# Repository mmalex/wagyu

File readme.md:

# 'wagyu' simple 5hp eurorack module to demonstrate STM32F405 based module design. 
## what is it?

WATCH THIS -  https://www.youtube.com/watch?v=Wm21Wc7AefM

a small eurorack module with 3 knobs, 4 DC coupled CV inputs (+-5v), an encoder, an 8x8 LED matrix display, stereo AC coupled outputs (+-8v), and stereo AC coupled audio rate inputs. the audio inputs are 'aliased' with two of the CV inputs, so that you can use one or both of them as either CV or audio inputs. for example, the 3 leftmost jacks can be used as CV inputs, then the 3 rightmost jacks are the 'audio' side, with mono in at the top and stereo out at the bottom. alternatively, the top two jacks can be used as stereo inputs.

it has an STM32F405 processor at 168Mhz, which is fast enough to do fun reverby, synthy things. it's also cheap and in-stock at JLC :)

## but what does it DO? 

it teaches me module design, and latterly, you - thru a series of (so far 2) youtube streams.

this repo is a dump of the state of the hardware design files and software as written on-stream.
the first stream was more hardware centric, but not about this specific design - https://www.youtube.com/watch?v=Xf4CxC8exFM
the second stream covered bringing up the entire sw/ folder from scratch for this design - https://www.youtube.com/watch?v=Wm21Wc7AefM

## Hardware
the files are presented in the exact state I showed on stream and submitted to JLCPCB for PCB manufacture and assembly. at the time, all SMT parts were in-stock and from their standard library. the front panel is presented as two designs that can be broken apart. I wasnt sure if 'holes' or 'no-solder-mask-circuitboard' would be better; in the end, only holes worked - so if you are submitting this, you can save yourself some money by removing the 'no-holes' half of the front panel design, by editing the kicad files and regenerating the gerbers.

the main board is a 4 layer design, mostly auto routed (sorry not sorry). It has 3 mistakes, none fatal: the euro power jack isnt perfectly centered, which causes the plastic plug to overhang by a mm or so. annoying, and could be fixed by shuffling it over a bit. it's fine if your case or the adjacent module has a bit of space there :). the I2C bus doesn't have pullups, oops; you need two 2.2k resistors pulling up to 3v3 adding. I work around this in software so it works fine without (I bit bang the I2C and go slow, using the STM's on-chip pullups). lastly, the footprint of the 8x8 LED matrix I mistakenly assumed the pins were in a square; they are not. see second video for more info, but you can just bend them and it fits. Just.

## BOM
all the SMT positioning (csv) that you can upload to JLC's assembly service is in the assembly/ subfolder; likewise, the SMT BOM with part numbers for the lcsc.com site - all chosen to be available for JLC assembly.
Once you receive the board, you need to source and add your own 'hardware':
- 3 linear taper pots, 50k -100k maybe? I got mine from thonk.co.uk, Vertical T-18 https://www.thonk.co.uk/shop/alpha-9mm-pots-vertical-t18/
- 6 thonkiconn jacks, also from thonk.co.uk
- an encoder with clicky button. eg https://www.digikey.co.uk/product-detail/en/bourns-inc/PEC11R-4215F-S0024/PEC11R-4215F-S0024-ND/4499665
- some knobs! from thonk.co.uk again.
- a 0.8" LED 8x8 matrix (single color). I got mine from adafruit, it says 'luckylight' on the side. mine was white, here's a red one: https://www.adafruit.com/product/454. in the UK, pimeroni is a great stockist of adafruit stuff.
- a eurorack 8x2 0.1" spacing male pin header for power. I stupidly soldered a right angled one onto mine- it does fit! but simpler would have just been to use bog standard 0.1" header pins, in 2 rows, and make sure to plug them into a plug before soldering to keep them at the right angle. I object to regulating 12v straight down to 3v3 and boiling the oceans - so its a 16 pin plug (for 5v). tough!
- a programming header - I use the 'STDC14 pinout' (google it), which puts a Uart along with classic SWD pins. The PCB expects a surface mount 7x2 0.05" spacing pin header. for example https://www.digikey.co.uk/product-detail/en/amphenol-icc-fci/20021121-00014T4LF/609-3730-ND/2209080. or you can just solder 4 bodge wires on over to your SWD programmer.

## SW
the software is as I left it at the end of the second stream. We've brought up all the hardware except audio input; the only files that differ from the autogenerated project are main.c and codec.h; everything else is ignorable boilerplate.
it doesn't do anything musical at this stage, but it should make a good starting point.

## stuff you might need
you need STMCube32IDE for free from ST.com to do the software side; runs on mac, windows and linux.
I used a Digilent Analog Discovery 2 as a scope & signal generator, but you don't strictly need it.
you will need some way to flash your board - an ST Link programmer for example; the new ST Link 3 Mini has exactly the right programming header, but I can't seem to find one to buy! instead, I use Nucleo boards (look on amazon for 'nucleo STM32') - they are typically under £20, give you a great prototyping platform AND a built in ST Link programmer you can use on your own standalone boards.

have fun! let me know on twitter if you get something out of this! twitter.com/mmalex

## License
I'm releasing this all into the public domain. the hardware is heavily inspired by the eurorack open source modules, and the codec & cpu parts are pretty generic.  I would appreciate if you let me know if you get any value out of this! let me know on twitter @mmalex.

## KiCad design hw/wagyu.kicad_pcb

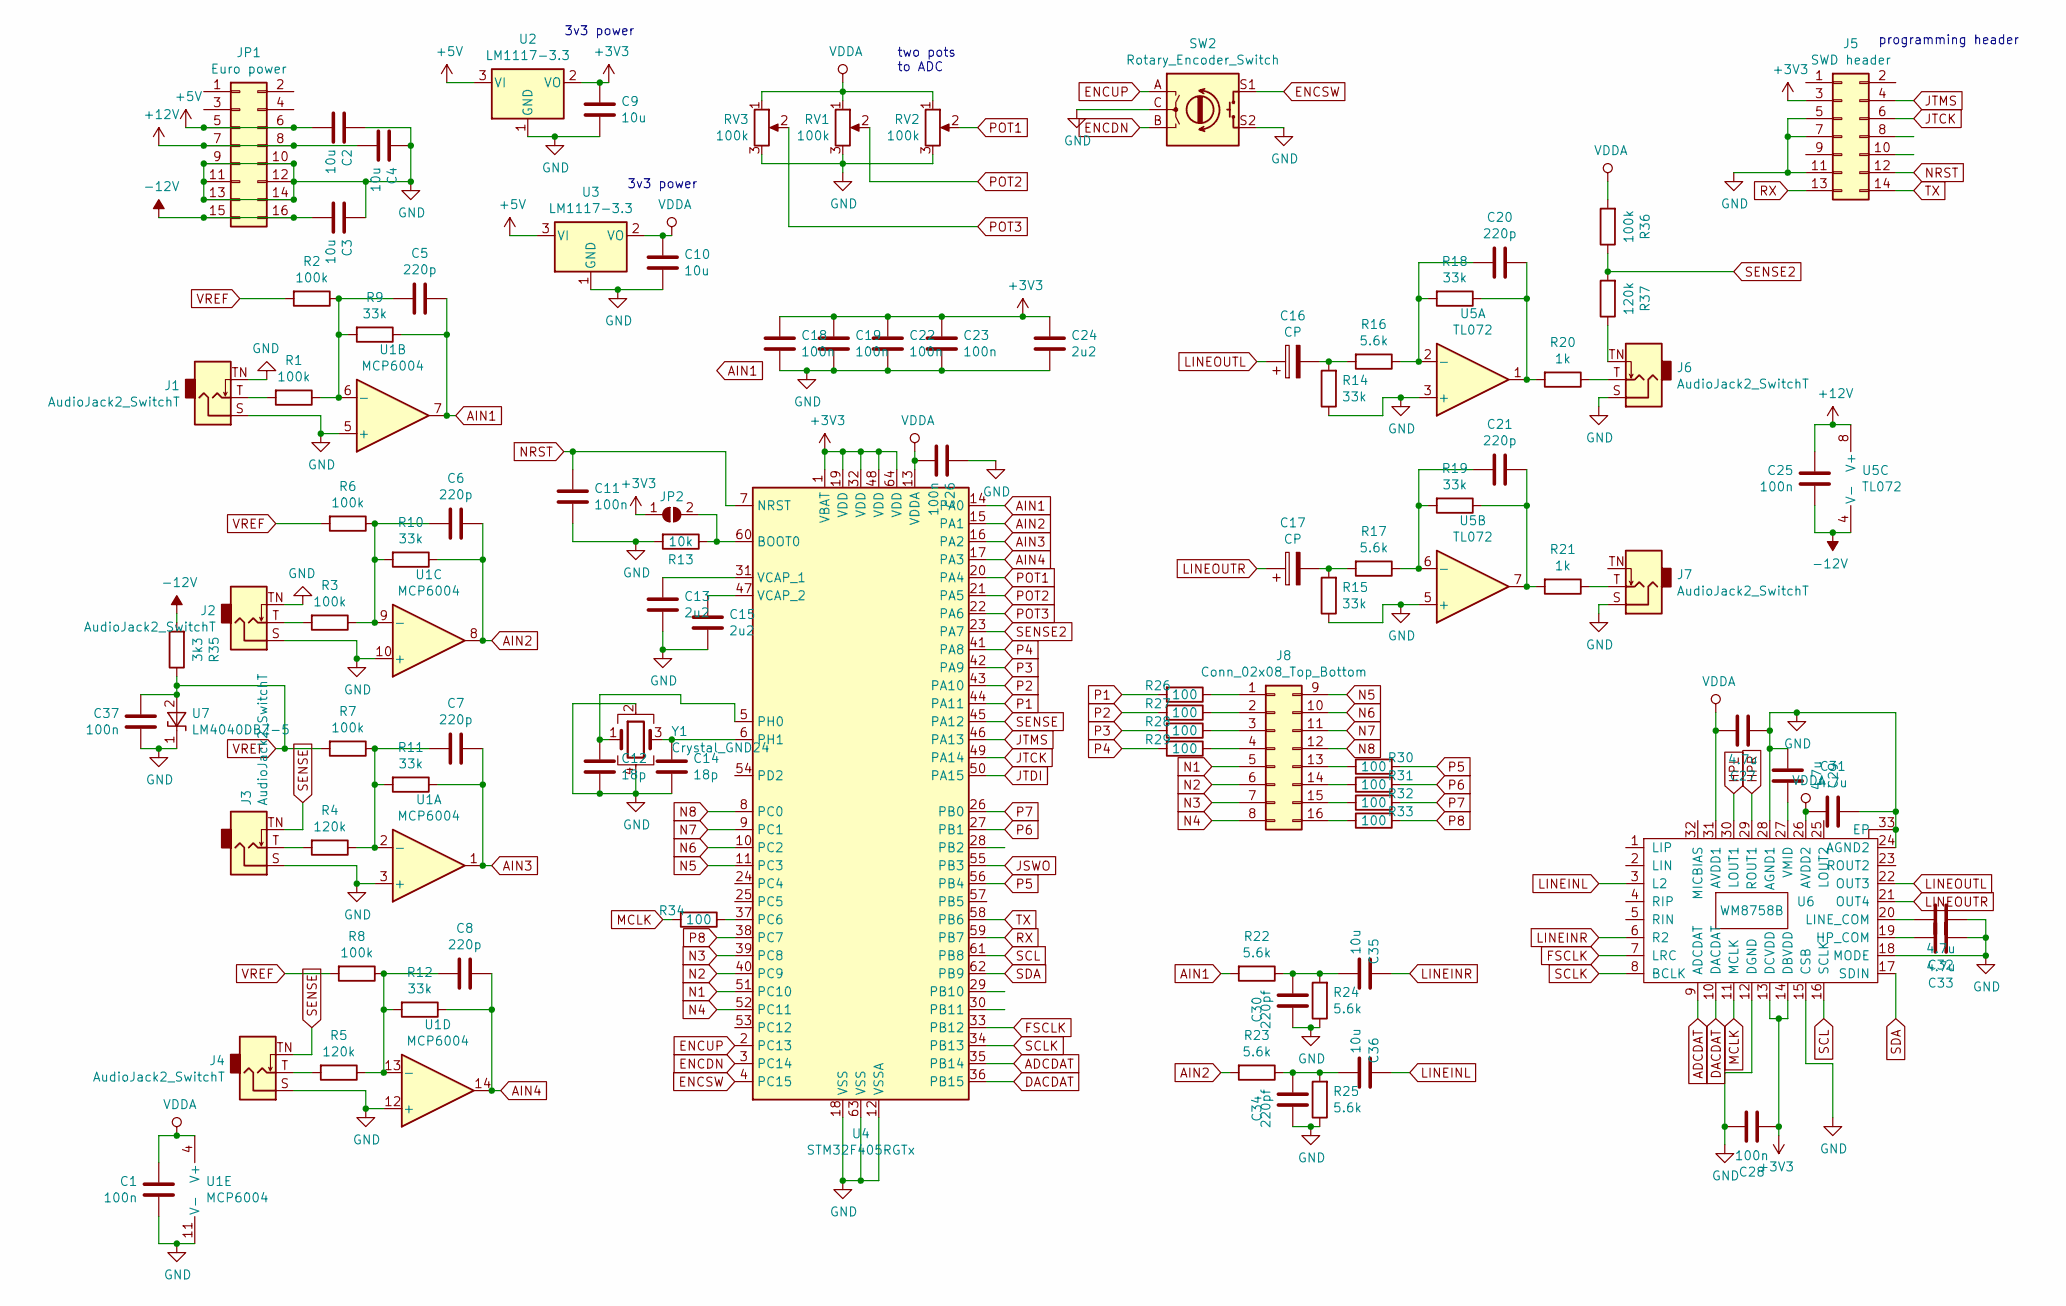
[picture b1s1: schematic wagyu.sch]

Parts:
C1, C11, C18, C19, C22, C23, C25, C26, C37: 100n; C_0603_1608Metric
C2, C3, C4, C9, C10, C35, C36: 10u; C_0805_2012Metric
C5, C6, C7, C8, C20, C21: 220p; C_0603_1608Metric
C12, C14: 18p; C_0603_1608Metric
C13, C15, C24: 2u2; C_0603_1608Metric
C16, C17: CP; CP_Elec_5x4.5
C27, C29, C31, C32, C33: 4.7u; C_0603_1608Metric
C28: 100n; C_0603_1608Metric; LCSC C19666
C30, C34: 220pf; C_0603_1608Metric
J1, J2, J3, J4, J6, J7: AudioJack2_SwitchT; Jack_3.5mm_QingPu_WQP-PJ398SM_Vertical_CircularHoles
J5: SWD header; PinHeader_2x07_P1.27mm_Vertical_SMD
J8: Conn_02x08_Top_Bottom; led8x8
JP1: Euro power; PinHeader_2x08_P2.54mm_Vertical
JP2: SolderJumper_2_Open; SolderJumper-2_P1.3mm_Open_Pad1.0x1.5mm
R1, R2, R3, R6, R7, R8, R36: 100k; R_0603_1608Metric
R4, R5, R37: 120k; R_0603_1608Metric
R9, R10, R11, R12, R14, R15, R18, R19: 33k; R_0603_1608Metric
R13: 10k; R_0603_1608Metric
R16, R17, R22, R23, R24, R25: 5.6k; R_0603_1608Metric
R20, R21: 1k; R_0603_1608Metric
R26, R27, R28, R29, R30, R31, R32, R33, R34: 100; R_0603_1608Metric
R35: 3k3; R_0603_1608Metric
RV1, RV2, RV3: 100k; Potentiometer_Alpha_RD901F-40-00D_Single_Vertical
SW2: Rotary_Encoder_Switch; RotaryEncoder_Alps_EC11E-Switch_Vertical_H20mm
U1: MCP6004; TSSOP-14_4.4x5mm_P0.65mm
U2, U3: LM1117-3.3; SOT-223-3_TabPin2
U4: STM32F405RGTx; LQFP-64_10x10mm_P0.5mm
U5: TL072; SOIC-8_3.9x4.9mm_P1.27mm
U6: WM8758B; QFN-32-1EP_5x5mm_P0.5mm_EP3.45x3.45mm; LCSC C323840
U7: LM4040DBZ-5; SOT-23
Y1: Crystal_GND24; Crystal_SMD_Abracon_ABM8G-4Pin_3.2x2.5mm

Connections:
+3V3: C9.1, C18.1, C19.1, C22.1, C23.1, C24.1, C28.2, J5.3, JP2.1 (A), U2.2 (VO), U4.1 (VBAT), U4.19 (VDD), U4.32 (VDD), U4.48 (VDD), U4.64 (VDD), U6.13 (DCVDD), U6.14 (DBVDD)
+5V: C2.2, JP1.5, JP1.6, U2.3 (VI), U3.3 (VI)
+12V: C4.2, C25.2, JP1.7, JP1.8, U5.8 (V+)
-12V: C3.2, C25.1, JP1.15, JP1.16, R35.2, U5.4 (V-)
ADCDAT: U4.35 (PB14), U6.9 (ADCDAT)
AIN1: C5.1, R9.1, R22.2, U1.7, U4.14 (PA0)
AIN2: C6.1, R10.1, R23.2, U1.8, U4.15 (PA1)
AIN3: C7.1, R11.1, U1.1, U4.16 (PA2)
AIN4: C8.1, R12.1, U1.14, U4.17 (PA3)
DACDAT: U4.36 (PB15), U6.10 (DACDAT)
ENCDN: SW2.B, U4.3 (PC14)
ENCSW: SW2.S1, U4.4 (PC15)
ENCUP: SW2.A, U4.2 (PC13)
FSCLK: U4.33 (PB12), U6.7 (LRC)
GND: C1.1, C2.1, C3.1, C4.1, C9.2, C10.2, C11.2, C12.2, C13.2, C14.2, C15.2, C18.2, C19.2, C22.2, C23.2, C24.2, C26.1, C27.2, C28.1, C29.2, C30.1, C31.1, C32.2, C33.2, C34.1, C37.1, J1.S, J1.TN, J2.S, J2.TN, J3.S, J4.S, J5.5, J5.7, J5.11, J6.S, J7.S, JP1.9, JP1.10, JP1.11, JP1.12, JP1.13, JP1.14, R13.2, R14.1, R15.1, R24.1, R25.1, RV1.3, RV2.3, RV3.3, SW2.C, SW2.S2, U1.3 (+), U1.5 (+), U1.10 (+), U1.11 (V-), U1.12 (+), U2.1 (GND), U3.1 (GND), U4.12 (VSSA), U4.18 (VSS), U4.63 (VSS), U5.3 (+), U5.5 (+), U6.12 (DGND), U6.15 (CSB), U6.18 (MODE), U6.24 (AGND2), U6.28 (AGND1), U6.33 (EP), U7.1 (K), Y1.2, Y1.4
HPL: U6.30 (LOUT1)
HPR: U6.29 (ROUT1)
JSWO: U4.55 (PB3)
JTCK: J5.6, U4.49 (PA14)
JTDI: U4.50 (PA15)
JTMS: J5.4, U4.46 (PA13)
LINEINL: C36.1, U6.3 (L2)
LINEINR: C35.1, U6.6 (R2)
LINEOUTL: C16.1, U6.22 (OUT3)
LINEOUTR: C17.1, U6.21 (OUT4)
MCLK: R34.2, U6.11 (MCLK)
N1: J8.5, U4.51 (PC10)
N2: J8.6, U4.40 (PC9)
N3: J8.7, U4.39 (PC8)
N4: J8.8, U4.52 (PC11)
N5: J8.9, U4.11 (PC3)
N6: J8.10, U4.10 (PC2)
N7: J8.11, U4.9 (PC1)
N8: J8.12, U4.8 (PC0)
NRST: C11.1, J5.12, U4.7 (NRST)
unnamed: C5.2, R1.1, R2.1, R9.2, U1.6 (-)
unnamed: C6.2, R3.1, R6.1, R10.2, U1.9 (-)
unnamed: C7.2, R4.1, R7.1, R11.2, U1.2 (-)
unnamed: C8.2, R5.1, R8.1, R12.2, U1.13 (-)
unnamed: C12.1, U4.5 (PH0), Y1.1
unnamed: C13.1, U4.31 (VCAP_1)
unnamed: C14.1, U4.6 (PH1), Y1.3
unnamed: C15.1, U4.47 (VCAP_2)
unnamed: C16.2, R14.2, R16.2
unnamed: C17.2, R15.2, R17.2
unnamed: C20.1, R18.1, R20.2, U5.1
unnamed: C20.2, R16.1, R18.2, U5.2 (-)
unnamed: C21.1, R19.1, R21.2, U5.7
unnamed: C21.2, R17.1, R19.2, U5.6 (-)
unnamed: C29.1, U6.27 (VMID)
unnamed: C30.2, C35.2, R22.1, R24.2
unnamed: C32.1, U6.20 (LINE_COM)
unnamed: C33.1, U6.19 (HP_COM)
unnamed: C34.2, C36.2, R23.1, R25.2
unnamed: J1.T, R1.2
unnamed: J2.T, R3.2
unnamed: J3.T, R4.2
unnamed: J4.T, R5.2
unnamed: J6.T, R20.1
unnamed: J6.TN, R37.1
unnamed: J7.T, R21.1
unnamed: J8.1, R26.1
unnamed: J8.2, R27.1
unnamed: J8.3, R28.1
unnamed: J8.4, R29.1
unnamed: J8.13, R30.1
unnamed: J8.14, R31.1
unnamed: J8.15, R32.1
unnamed: J8.16, R33.1
unnamed: JP2.2 (B), R13.1, U4.60 (BOOT0)
unnamed: R34.1, U4.37 (PC6)
P1: R26.2, U4.44 (PA11)
P2: R27.2, U4.43 (PA10)
P3: R28.2, U4.42 (PA9)
P4: R29.2, U4.41 (PA8)
P5: R30.2, U4.56 (PB4)
P6: R31.2, U4.27 (PB1)
P7: R32.2, U4.26 (PB0)
P8: R33.2, U4.38 (PC7)
POT1: RV2.2, U4.20 (PA4)
POT2: RV1.2, U4.21 (PA5)
POT3: RV3.2, U4.22 (PA6)
RX: J5.13, U4.59 (PB7)
SCL: U4.61 (PB8), U6.16 (SCLK)
SCLK: U4.34 (PB13), U6.8 (BCLK)
SDA: U4.62 (PB9), U6.17 (SDIN)
SENSE: J3.TN, J4.TN, U4.45 (PA12)
SENSE2: R36.1, R37.2, U4.23 (PA7)
TX: J5.14, U4.58 (PB6)
VDDA: C1.2, C10.1, C26.2, C27.1, C31.2, R36.2, RV1.1, RV2.1, RV3.1, U1.4 (V+), U3.2 (VO), U4.13 (VDDA), U6.26 (AVDD2), U6.31 (AVDD1)
VREF: C37.2, R2.2, R6.2, R7.2, R8.2, R35.1, U7.2 (A)

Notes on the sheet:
two pots to ADC
3v3 power
programming header

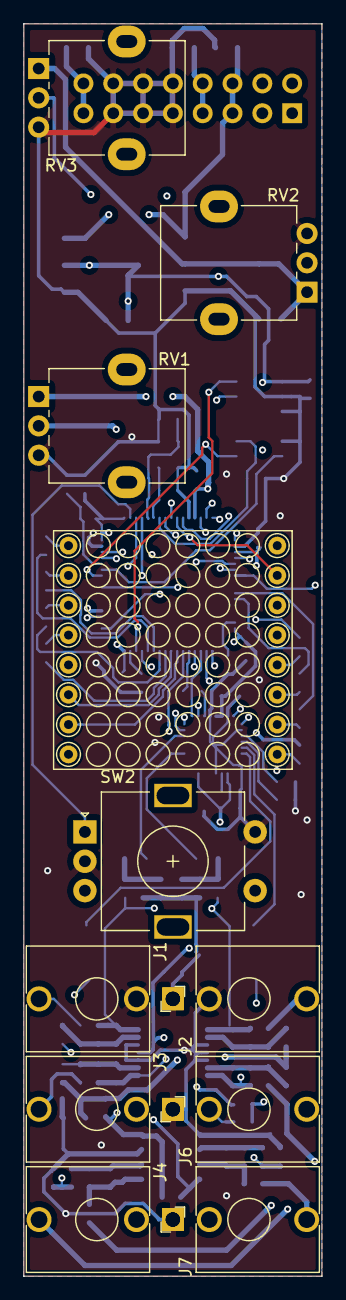
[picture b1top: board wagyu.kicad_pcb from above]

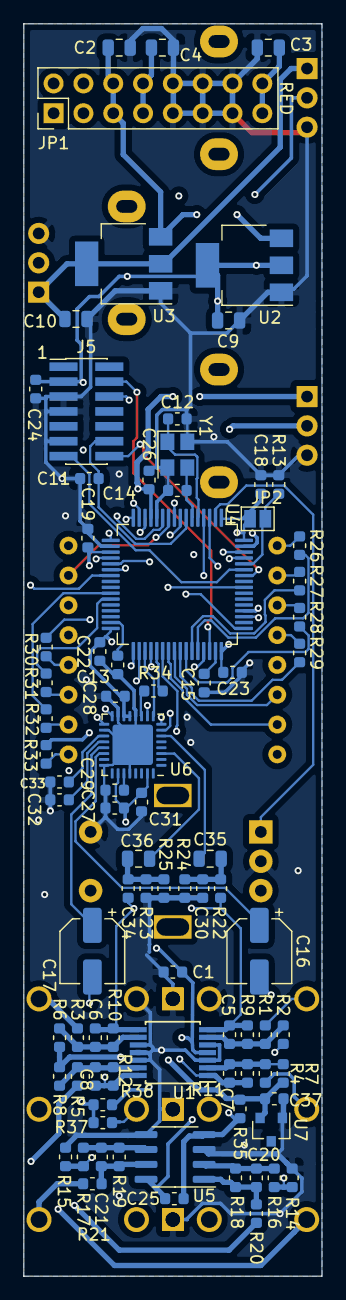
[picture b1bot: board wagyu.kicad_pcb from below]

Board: 4 copper layers, 25.4 x 106.7 mm, 96 parts (85 on the bottom side), 87 nets.

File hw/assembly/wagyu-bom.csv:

Comment,Designator,Footprint, LCSC
100n,"C1,C25,C11,C18,C19,C22,C23,C26,C28,C37",Capacitor_SMD:C_0603_1608Metric,C14663
2u2,"C13,C15,C24",Capacitor_SMD:C_0603_1608Metric,C23630
18p,"C14,C12",Capacitor_SMD:C_0603_1608Metric,C1647
10uf,"C16,C17",Capacitor_SMD:CP_Elec_5x4.5,C249452
4.7u,"C29,C27,C31,C32,C33",Capacitor_SMD:C_0603_1608Metric,C19666
220pf,"C30,C34",Capacitor_SMD:C_0603_1608Metric,C1603
220p,"C5,C6,C7,C8,C20,C21",Capacitor_SMD:C_0603_1608Metric,C1603
10u,"C9,C4,C3,C2,C10,C35,C36",Capacitor_SMD:C_0805_2012Metric,C15850
100k,"R1,R3,R2,R6,R7,R8,R36",Resistor_SMD:R_0603_1608Metric,C25803
10k,R13,Resistor_SMD:R_0603_1608Metric,C25804
5.6k,"R16,R17,R24,R22,R25,R23",Resistor_SMD:R_0603_1608Metric,C23189
1k,"R20,R21",Resistor_SMD:R_0603_1608Metric,C21190
100,"R26,R27,R28,R29,R30,R31,R32,R33,R34",Resistor_SMD:R_0603_1608Metric,C22775
3k3,R35,Resistor_SMD:R_0603_1608Metric,C22978
120k,"R4,R5,R37",Resistor_SMD:R_0603_1608Metric,C25808
33k,"R9,R10,R11,R12,R18,R14,R19,R15",Resistor_SMD:R_0603_1608Metric,C4216
MCP6004,U1,Package_SO:TSSOP-14_4.4x5mm_P0.65mm,C50282
LM1117-3.3,"U2,U3",Package_TO_SOT_SMD:SOT-223-3_TabPin2,C6186
STM32F405RGTx,U4,Package_QFP:LQFP-64_10x10mm_P0.5mm,C15742
TL072,U5,Package_SO:SOIC-8_3.9x4.9mm_P1.27mm,C6961
WM8758B,U6,Package_DFN_QFN:QFN-32-1EP_5x5mm_P0.5mm_EP3.45x3.45mm,C323840
LM4040DBZ-5,U7,Package_TO_SOT_SMD:SOT-23,C156291
Crystal_GND24,Y1,Crystal:Crystal_SMD_Abracon_ABM8G-4Pin_3.2x2.5mm,C13738

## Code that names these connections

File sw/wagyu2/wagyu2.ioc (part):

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Mcu.Name=STM32F405RGTx
Mcu.Package=LQFP64
Mcu.UserName=STM32F405RGTx
PA0-WKUP.Signal=ADCx_IN0
PA1.Signal=ADCx_IN1
PA10.Signal=S_TIM1_CH3
PA11.Signal=S_TIM1_CH4
PA13.Mode=Serial_Wire
PA13.Signal=SYS_JTMS-SWDIO
PA14.Mode=Serial_Wire
PA14.Signal=SYS_JTCK-SWCLK
PA2.Signal=ADCx_IN2
PA3.Signal=ADCx_IN3
PA4.Signal=ADCx_IN4
PA5.Signal=ADCx_IN5
PA6.Signal=ADCx_IN6
PA8.Signal=S_TIM1_CH1
PA9.Signal=S_TIM1_CH2
PB0.Signal=S_TIM3_CH3
PB1.Signal=S_TIM3_CH4
PB12.Mode=Full_Duplex_Master
PB12.Signal=I2S2_WS
PB13.Mode=Full_Duplex_Master
PB13.Signal=I2S2_CK
PB14.Mode=Full_Duplex_Master
PB14.Signal=I2S2_ext_SD
PB15.Mode=Full_Duplex_Master
PB15.Signal=I2S2_SD
PB4.Signal=S_TIM3_CH1
PB6.Mode=Asynchronous
PB6.Signal=USART1_TX
PB7.Mode=Asynchronous
PB7.Signal=USART1_RX
PB8.GPIOParameters=PinState,GPIO_PuPd,GPIO_ModeDefaultOutputPP
PB8.GPIO_ModeDefaultOutputPP=GPIO_MODE_OUTPUT_OD
PB8.GPIO_PuPd=GPIO_PULLUP
PB8.PinState=GPIO_PIN_SET
PB8.Signal=GPIO_Output
PB9.GPIOParameters=PinState,GPIO_PuPd,GPIO_ModeDefaultOutputPP
PB9.GPIO_ModeDefaultOutputPP=GPIO_MODE_OUTPUT_OD
PB9.GPIO_PuPd=GPIO_PULLUP
PB9.PinState=GPIO_PIN_SET
PB9.Signal=GPIO_Output
PC0.Signal=GPIO_Output
PC1.Signal=GPIO_Output
PC10.GPIOParameters=PinState
PC10.PinState=GPIO_PIN_SET
PC10.Signal=GPIO_Output
PC11.Signal=GPIO_Output
PC13-ANTI_TAMP.GPIOParameters=GPIO_PuPd,GPIO_ModeDefaultEXTI
PC13-ANTI_TAMP.GPIO_ModeDefaultEXTI=GPIO_MODE_IT_RISING_FALLING
PC13-ANTI_TAMP.GPIO_PuPd=GPIO_PULLUP
PC13-ANTI_TAMP.Signal=GPXTI13
PC14-OSC32_IN.GPIOParameters=GPIO_PuPd,GPIO_ModeDefaultEXTI
PC14-OSC32_IN.GPIO_ModeDefaultEXTI=GPIO_MODE_IT_RISING_FALLING
PC14-OSC32_IN.GPIO_PuPd=GPIO_PULLUP
PC14-OSC32_IN.Signal=GPXTI14
PC15-OSC32_OUT.GPIOParameters=GPIO_PuPd
PC15-OSC32_OUT.GPIO_PuPd=GPIO_PULLUP
PC15-OSC32_OUT.Signal=GPIO_Input
PC2.Signal=GPIO_Output
PC3.Signal=GPIO_Output
PC6.Mode=Master_Clock_Activated
PC6.Signal=I2S2_MCK
PC7.Signal=S_TIM3_CH2
PC8.Signal=GPIO_Output
PC9.Signal=GPIO_Output
PH0-OSC_IN.Mode=HSE-External-Oscillator
PH0-OSC_IN.Signal=RCC_OSC_IN
PH1-OSC_OUT.Mode=HSE-External-Oscillator
PH1-OSC_OUT.Signal=RCC_OSC_OUT
RCC.HSE_VALUE=16000000
RCC.SYSCLKFreq_VALUE=168000000
RCC.SYSCLKSource=RCC_SYSCLKSOURCE_PLLCLK
board=custom

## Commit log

2020-04-12 initial commit
    a bit of sw missing
2020-04-12 add missing files
